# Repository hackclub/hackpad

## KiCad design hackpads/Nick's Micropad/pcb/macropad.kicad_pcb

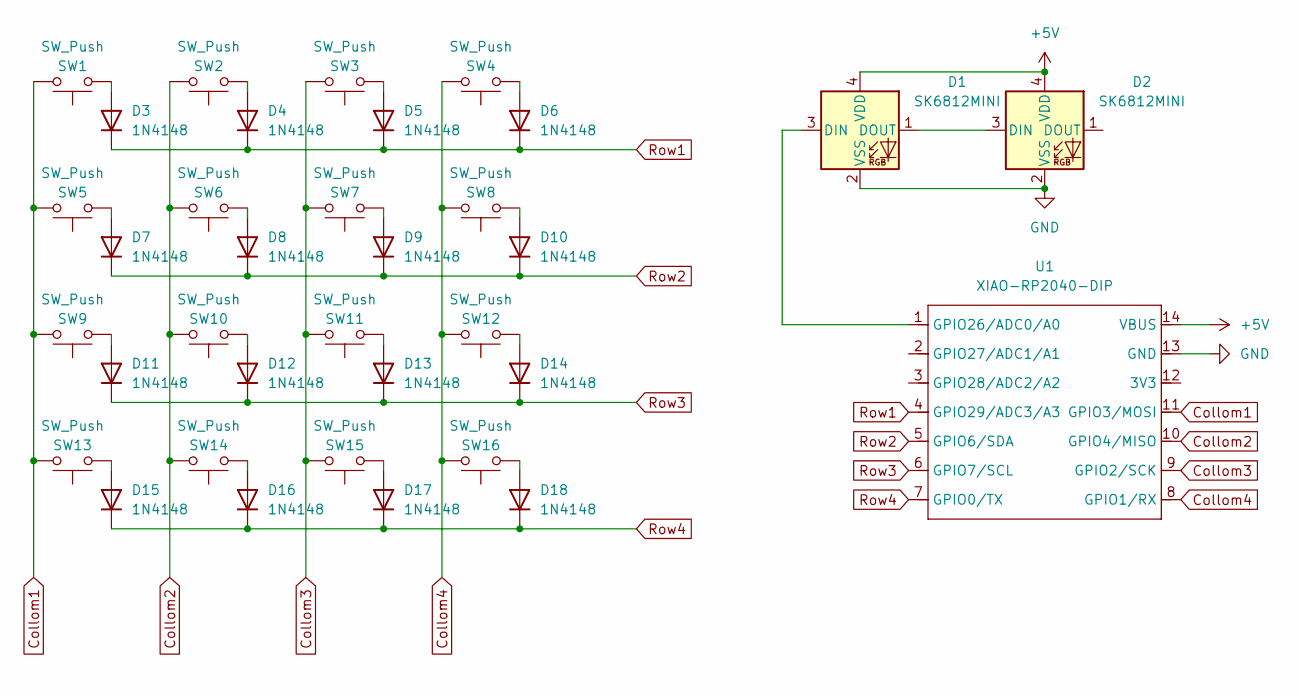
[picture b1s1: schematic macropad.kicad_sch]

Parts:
D1, D2: SK6812MINI; LED_SK6812MINI_PLCC4_3.5x3.5mm_P1.75mm
D3, D4, D5, D6, D7, D8, D9, D10, D11, D12, D13, D14, D15, D16, D17, D18: 1N4148; D_DO-35_SOD27_P7.62mm_Horizontal
SW1, SW2, SW3, SW4, SW5, SW6, SW7, SW8, SW9, SW10, SW11, SW12, SW13, SW14, SW15, SW16: SW_Push; SW_Cherry_MX_1.00u_PCB
U1: XIAO-RP2040-DIP

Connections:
+5V: D1.4 (VDD), D2.4 (VDD), U1.14 (VBUS)
Collom1: SW1.2, SW5.2, SW9.2, SW13.2, U1.11 (GPIO3/MOSI)
Collom2: SW2.2, SW6.2, SW10.2, SW14.2, U1.10 (GPIO4/MISO)
Collom3: SW3.2, SW7.2, SW11.2, SW15.2, U1.9 (GPIO2/SCK)
Collom4: SW4.2, SW8.2, SW12.2, SW16.2, U1.8 (GPIO1/RX)
GND: D1.2 (VSS), D2.2 (VSS), U1.13 (GND)
unnamed: D1.3 (DIN), U1.1 (GPIO26/ADC0/A0)
unnamed: D1.1 (DOUT), D2.3 (DIN)
unnamed: D3.2 (A), SW1.1
unnamed: D4.2 (A), SW2.1
unnamed: D5.2 (A), SW3.1
unnamed: D6.2 (A), SW4.1
unnamed: D7.2 (A), SW5.1
unnamed: D8.2 (A), SW6.1
unnamed: D9.2 (A), SW7.1
unnamed: D10.2 (A), SW8.1
unnamed: D11.2 (A), SW9.1
unnamed: D12.2 (A), SW10.1
unnamed: D13.2 (A), SW11.1
unnamed: D14.2 (A), SW12.1
unnamed: D15.2 (A), SW13.1
unnamed: D16.2 (A), SW14.1
unnamed: D17.2 (A), SW15.1
unnamed: D18.2 (A), SW16.1
Row1: D3.1 (K), D4.1 (K), D5.1 (K), D6.1 (K), U1.4 (GPIO29/ADC3/A3)
Row2: D7.1 (K), D8.1 (K), D9.1 (K), D10.1 (K), U1.5 (GPIO6/SDA)
Row3: D11.1 (K), D12.1 (K), D13.1 (K), D14.1 (K), U1.6 (GPIO7/SCL)
Row4: D15.1 (K), D16.1 (K), D17.1 (K), D18.1 (K), U1.7 (GPIO0/TX)

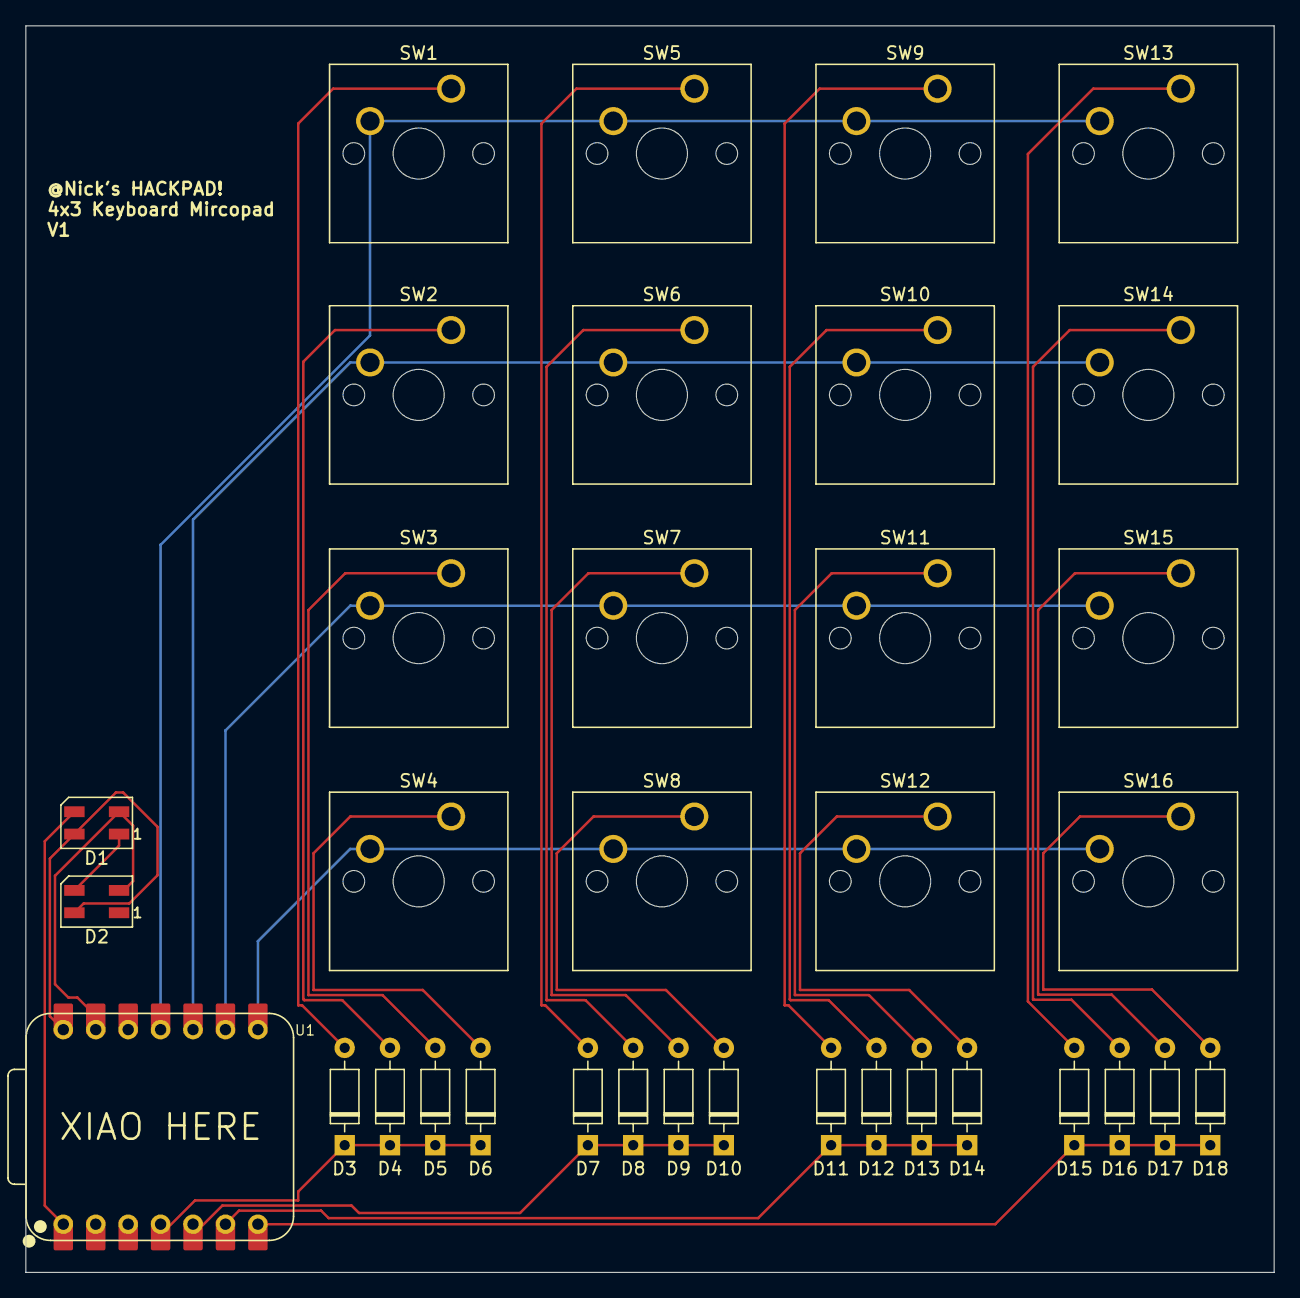
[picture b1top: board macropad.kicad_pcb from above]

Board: 2 copper layers, 97.8 x 97.6 mm, 35 parts (0 on the bottom side), 28 nets.

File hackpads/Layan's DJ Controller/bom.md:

# Hackpad - Bill of Materials

- 1x XIAO SEEED RP2040: XIAO-RP2040-DIP
- 1x MCP23017-SO: Package_SO:SOIC-28W_7.5x17.9mm_P1.27mm
- 2x LEDs: LED_SK6812MINI_PLCC4_3.5x3.5mm_P1.75mm
- 2x Bourns slide potentiometer: TRIM_PTA4543-2015DPA103
- 2x 4.7kΩ resistors: R_Axial_DIN0204_L3.6mm_D1.6mm_P7.62mm_Horizontal
- 8x Cherry MX switches: SW_Cherry_MX_1.00u_PCB
- 2x Alps rotary encoders: RotaryEncoder_Alps_EC11E_Vertical_H20mm

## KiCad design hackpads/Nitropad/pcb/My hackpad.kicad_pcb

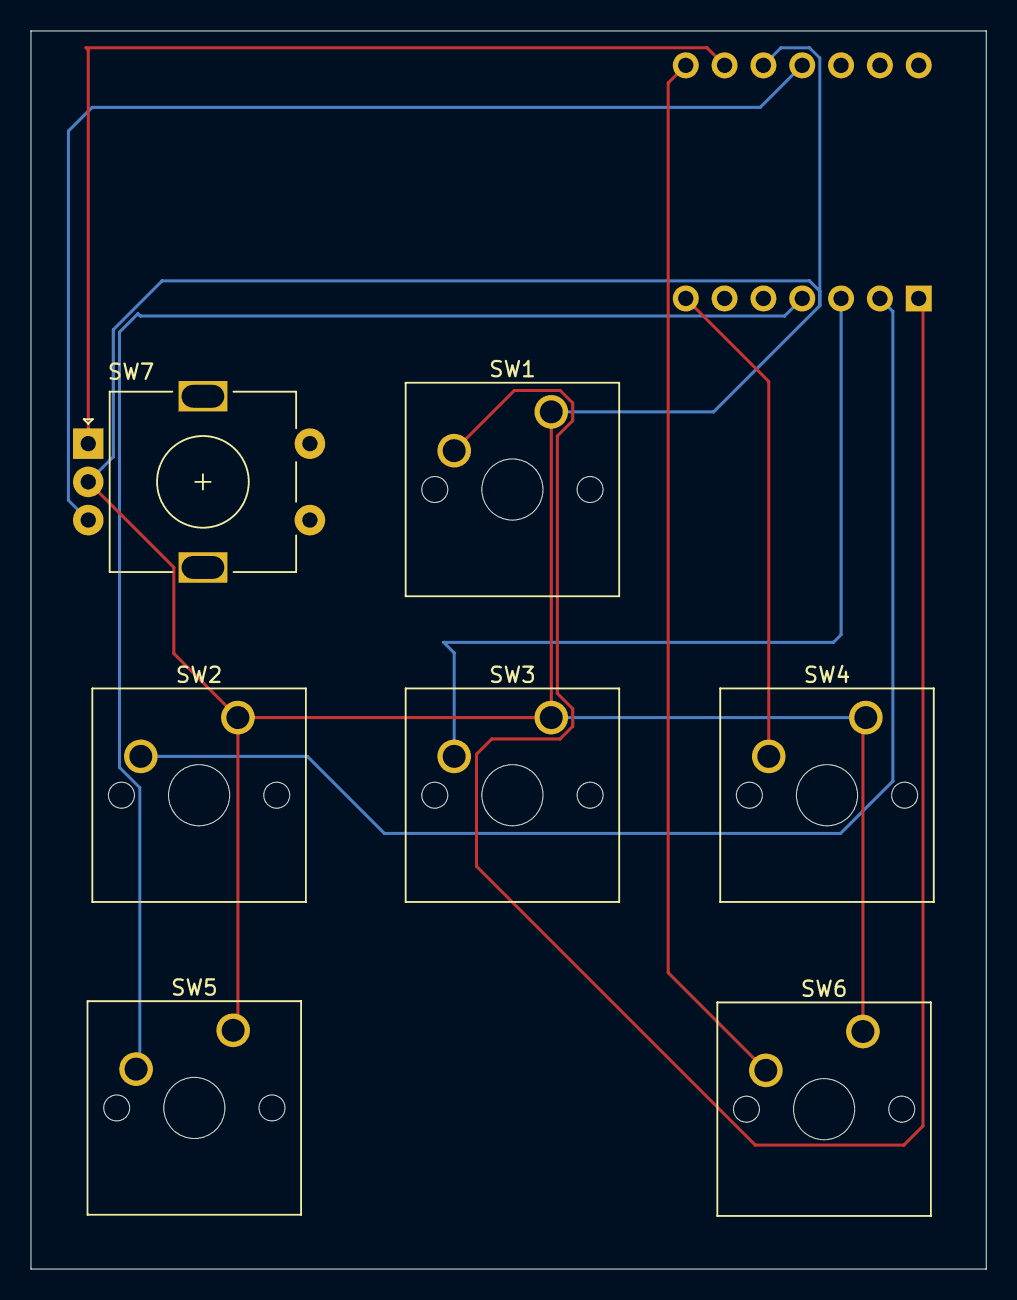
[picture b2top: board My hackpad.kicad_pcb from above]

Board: 2 copper layers, 62.5 x 81.0 mm, 8 parts (1 on the bottom side), 9 nets.

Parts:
SW1, SW2, SW3, SW4, SW5, SW6: SW_Push; SW_Cherry_MX_1.00u_PCB
SW7: RotaryEncoder; RotaryEncoder_Alps_EC11E-Switch_Vertical_H20mm
U1: Seeed Studio XIAO SAMD21; XIAO-Generic-Thruhole-14P-2.54-21X17.8MM

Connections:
1: SW1.2, U1.1 (PA02_A0_D0)
2: SW2.2, U1.2 (PA4_A1_D1)
3: SW3.2, U1.3 (PA10_A2_D2)
4: SW5.2, U1.4 (PA11_A3_D3)
5: SW4.2, U1.7 (PB08_A6_D6_TX)
6: SW6.2, U1.8 (PB09_A7_D7_RX)
A: SW7.A, U1.9 (PA7_A8_D8_SCK)
B: SW7.B, U1.11 (PA6_A10_D10_MOSI)
GND: SW1.1, SW2.1, SW3.1, SW4.1, SW5.1, SW6.1, SW7.C, U1.10 (PA5_A9_D9_MISO)

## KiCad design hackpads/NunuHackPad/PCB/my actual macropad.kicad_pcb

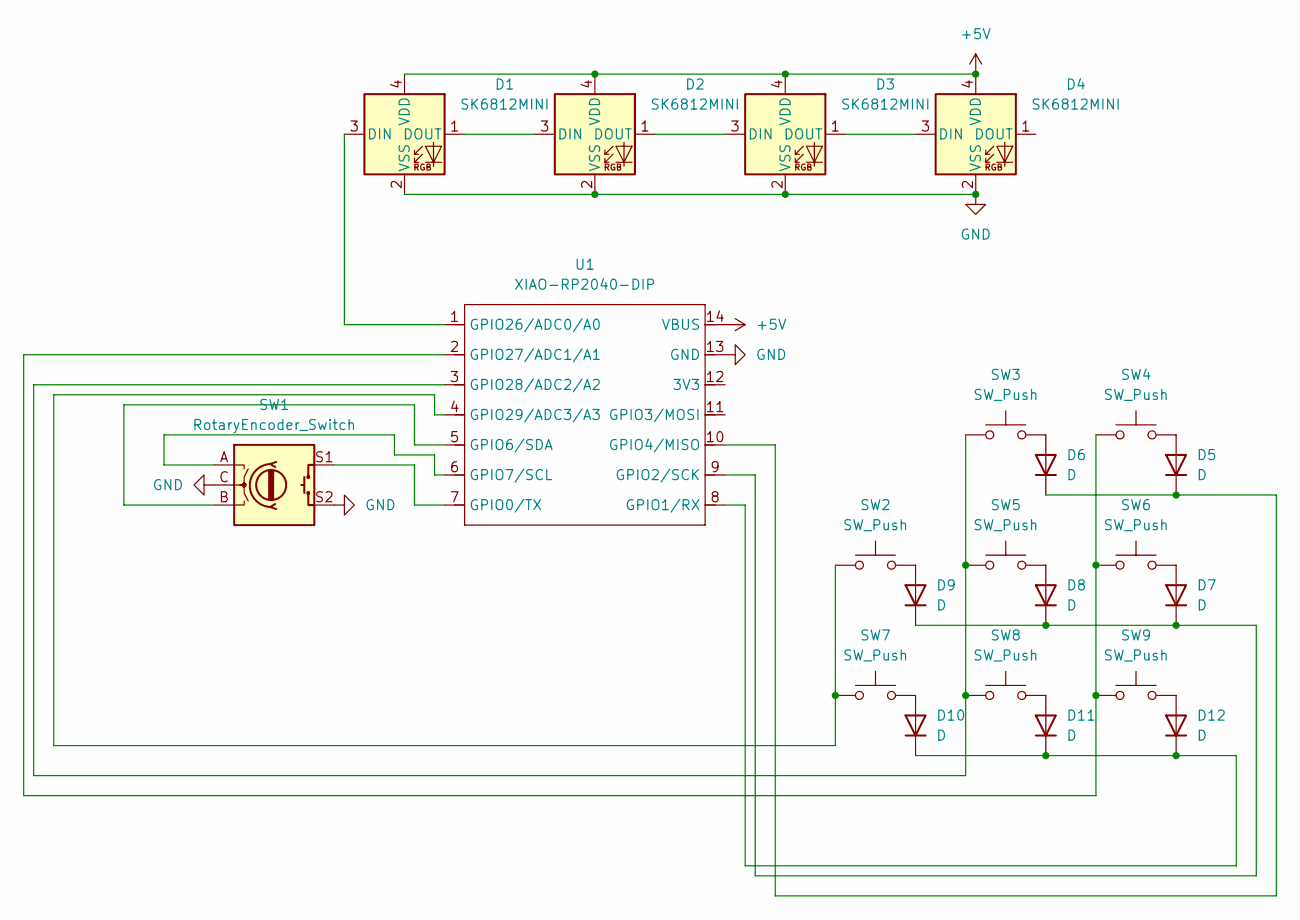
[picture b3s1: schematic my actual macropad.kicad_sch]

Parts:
D1, D2, D3, D4: SK6812MINI; LED_SK6812MINI_PLCC4_3.5x3.5mm_P1.75mm
D5, D6, D7, D8, D9, D10, D11, D12: D; D_DO-35_SOD27_P7.62mm_Horizontal
SW1: RotaryEncoder_Switch; RotaryEncoder_Alps_EC11E-Switch_Vertical_H20mm_CircularMoun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
SW2, SW3, SW4, SW5, SW6, SW7, SW8, SW9: SW_Push; SW_Cherry_MX_1.00u_PCB_3D
U1: XIAO-RP2040-DIP; XIAO-RP2040-DIP-3D

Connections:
+5V: D1.4 (VDD), D2.4 (VDD), D3.4 (VDD), D4.4 (VDD), U1.14 (VBUS)
GND: D1.2 (VSS), D2.2 (VSS), D3.2 (VSS), D4.2 (VSS), SW1.C, SW1.S2, U1.13 (GND)
unnamed: D1.3 (DIN), U1.1 (GPIO26/ADC0/A0)
unnamed: D1.1 (DOUT), D2.3 (DIN)
unnamed: D2.1 (DOUT), D3.3 (DIN)
unnamed: D3.1 (DOUT), D4.3 (DIN)
unnamed: D5.2 (A), SW4.2
unnamed: D5.1 (K), D6.1 (K), U1.10 (GPIO4/MISO)
unnamed: D6.2 (A), SW3.2
unnamed: D7.2 (A), SW6.2
unnamed: D7.1 (K), D8.1 (K), D9.1 (K), U1.9 (GPIO2/SCK)
unnamed: D8.2 (A), SW5.2
unnamed: D9.2 (A), SW2.2
unnamed: D10.2 (A), SW7.2
unnamed: D10.1 (K), D11.1 (K), D12.1 (K), U1.8 (GPIO1/RX)
unnamed: D11.2 (A), SW8.2
unnamed: D12.2 (A), SW9.2
unnamed: SW1.S1, U1.7 (GPIO0/TX)
unnamed: SW1.B, U1.5 (GPIO6/SDA)
unnamed: SW1.A, U1.6 (GPIO7/SCL)
unnamed: SW4.1, SW6.1, SW9.1, U1.2 (GPIO27/ADC1/A1)
unnamed: SW3.1, SW5.1, SW8.1, U1.3 (GPIO28/ADC2/A2)
unnamed: SW2.1, SW7.1, U1.4 (GPIO29/ADC3/A3)

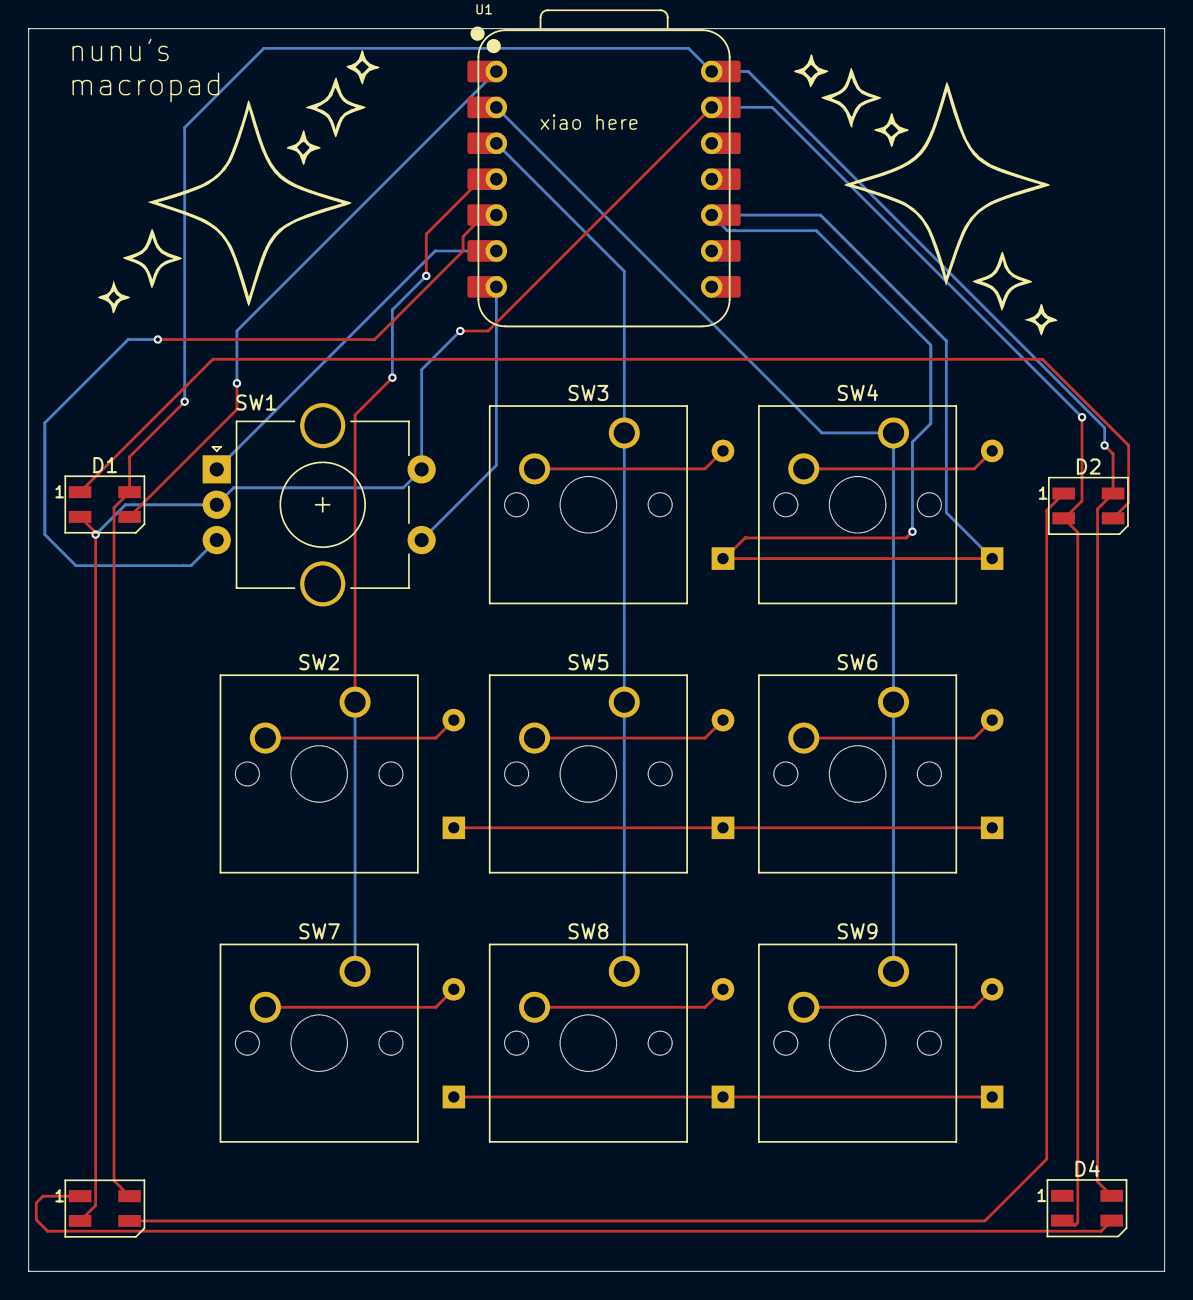
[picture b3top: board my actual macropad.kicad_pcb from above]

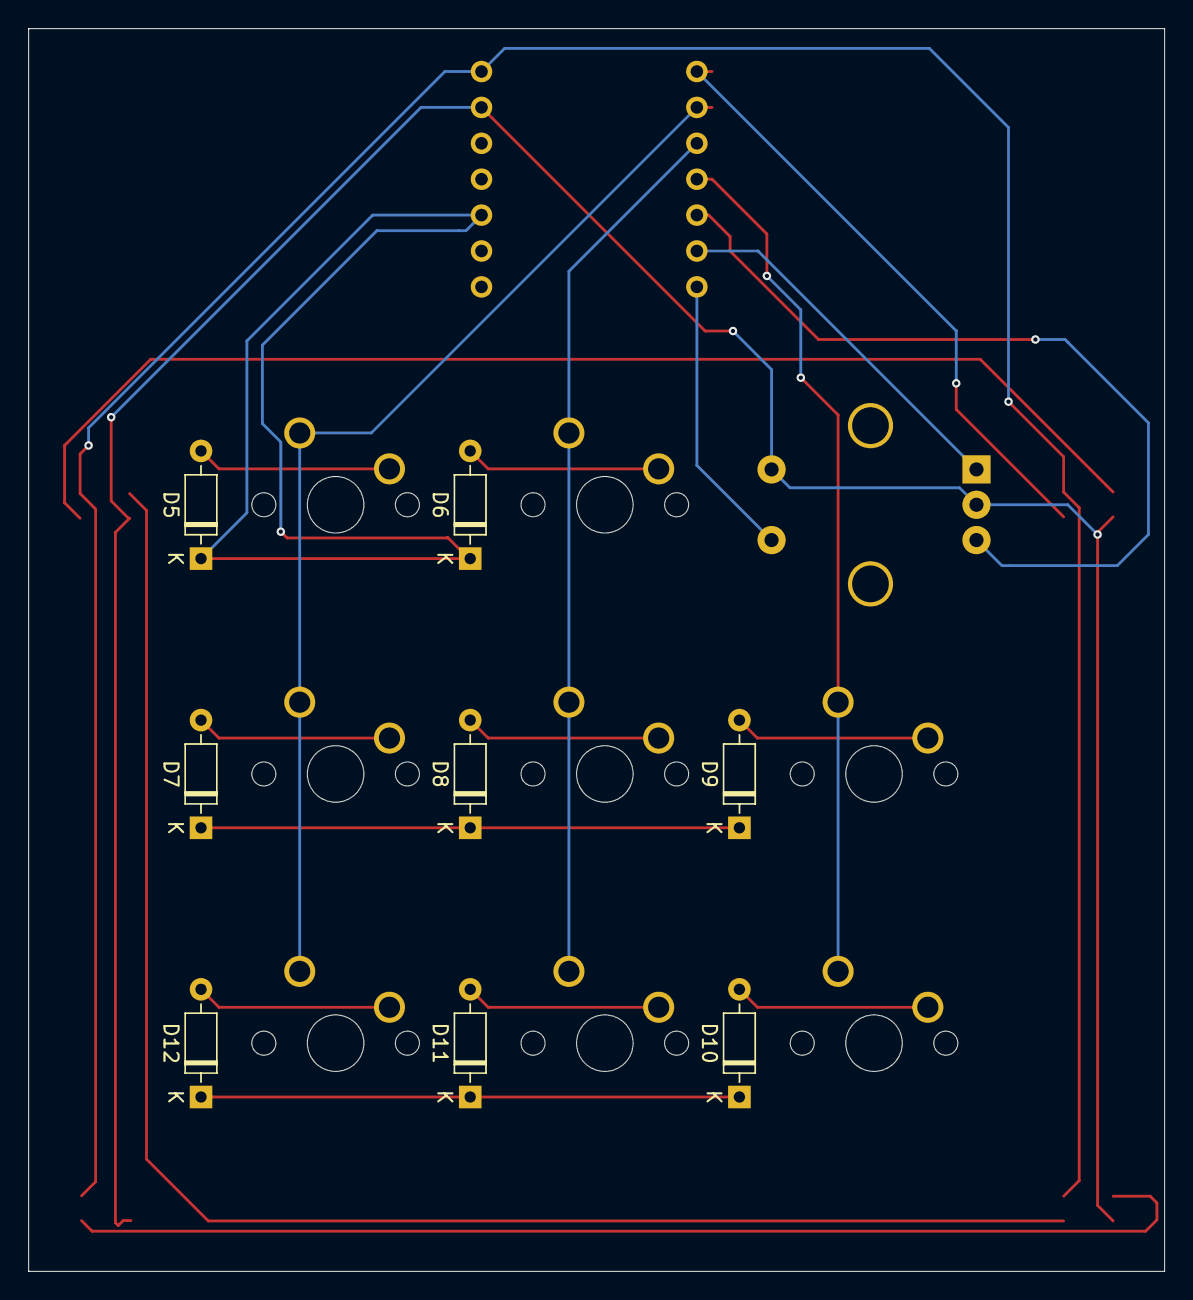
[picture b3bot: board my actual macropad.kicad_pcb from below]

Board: 2 copper layers, 80.4 x 87.9 mm, 22 parts (8 on the bottom side), 23 nets.

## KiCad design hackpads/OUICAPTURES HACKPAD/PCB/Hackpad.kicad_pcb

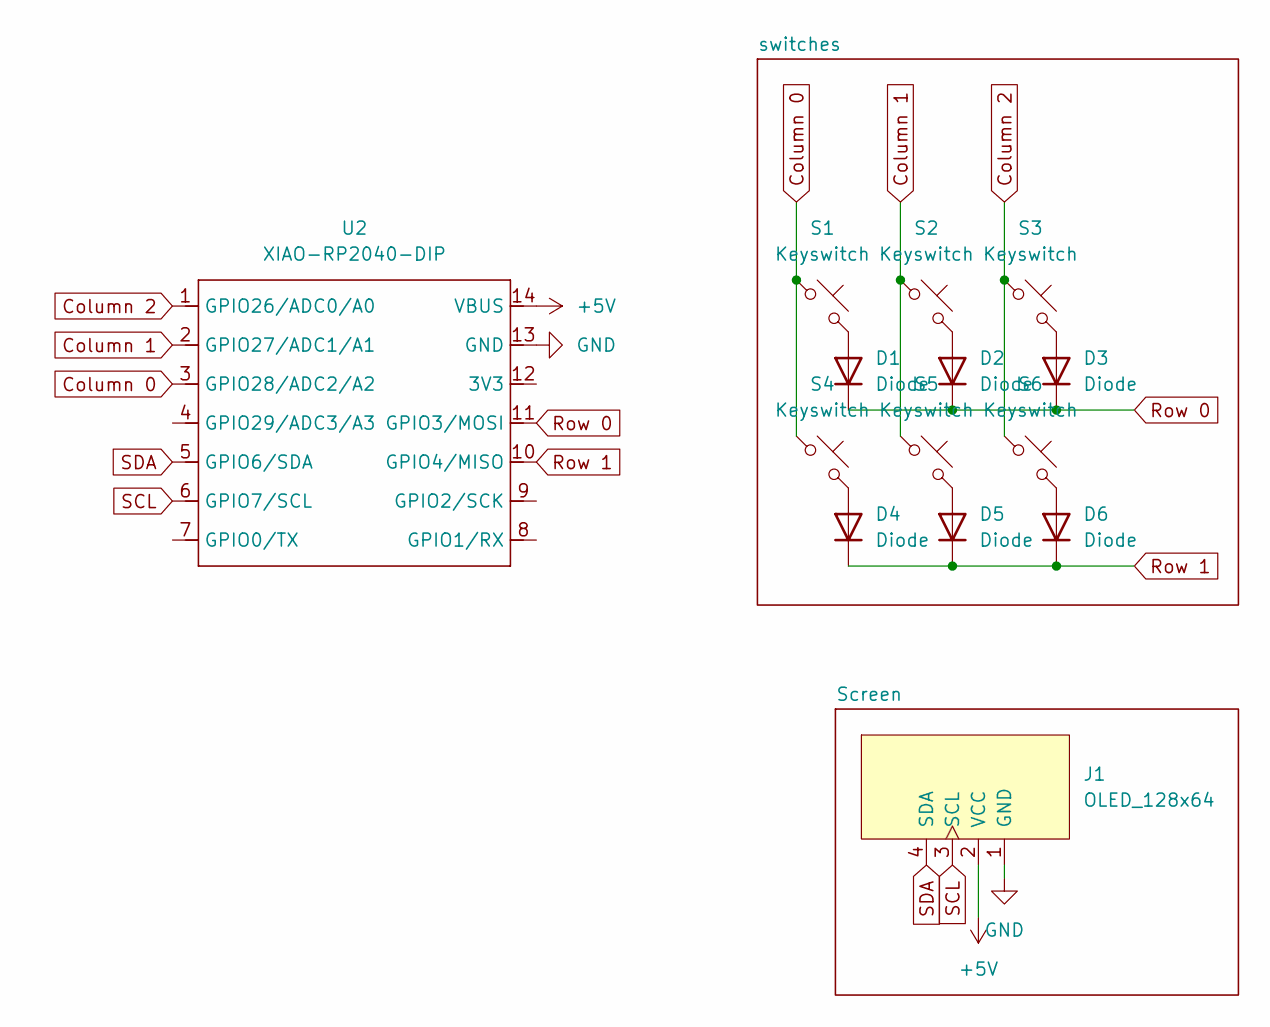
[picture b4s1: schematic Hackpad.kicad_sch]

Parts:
D1, D2, D3, D4, D5, D6: Diode; Diode_DO-35
J1: OLED_128x64
S1, S2, S3, S4, S5, S6: Keyswitch; MX_PCB_1.00u
U2: XIAO-RP2040-DIP; Seeed_XIAO_RP2040

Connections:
+5V: J1.2 (VCC), U2.14 (VBUS)
Column 0: S1.1, S4.1, U2.3 (GPIO28/ADC2/A2)
Column 1: S2.1, S5.1, U2.2 (GPIO27/ADC1/A1)
Column 2: S3.1, S6.1, U2.1 (GPIO26/ADC0/A0)
GND: J1.1 (GND), U2.13 (GND)
unnamed: D1.2 (A), S1.2
unnamed: D2.2 (A), S2.2
unnamed: D3.2 (A), S3.2
unnamed: D4.2 (A), S4.2
unnamed: D5.2 (A), S5.2
unnamed: D6.2 (A), S6.2
Row 0: D1.1 (K), D2.1 (K), D3.1 (K), U2.11 (GPIO3/MOSI)
Row 1: D4.1 (K), D5.1 (K), D6.1 (K), U2.10 (GPIO4/MISO)
SCL: J1.3 (SCL), U2.6 (GPIO7/SCL)
SDA: J1.4 (SDA), U2.5 (GPIO6/SDA)

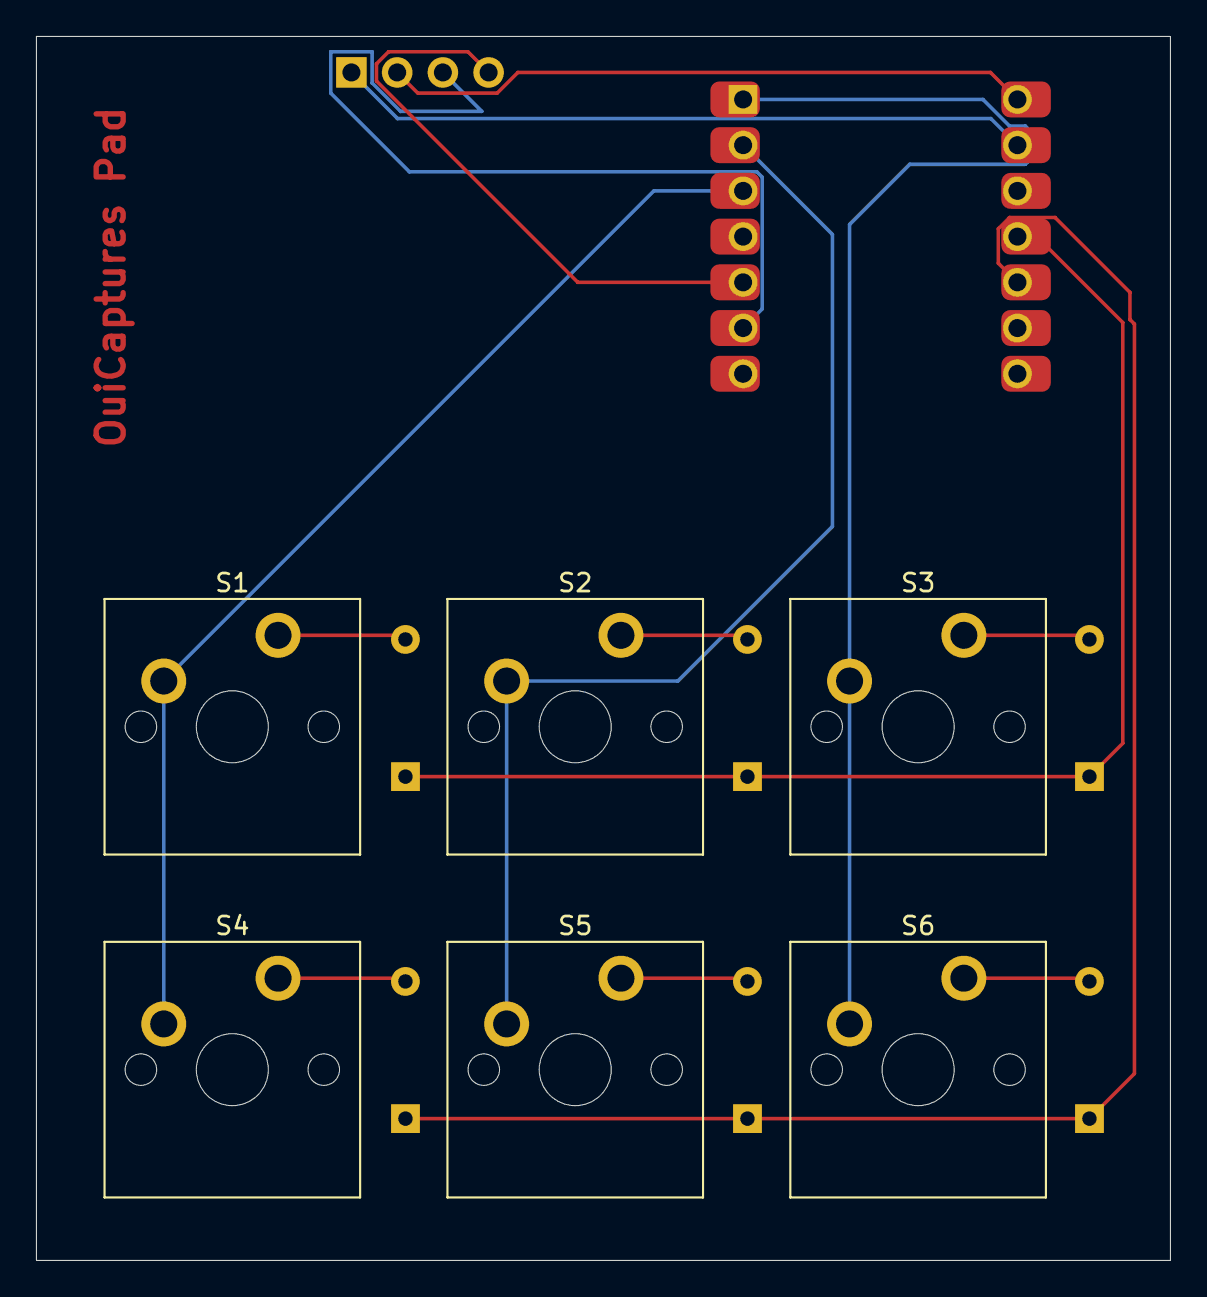
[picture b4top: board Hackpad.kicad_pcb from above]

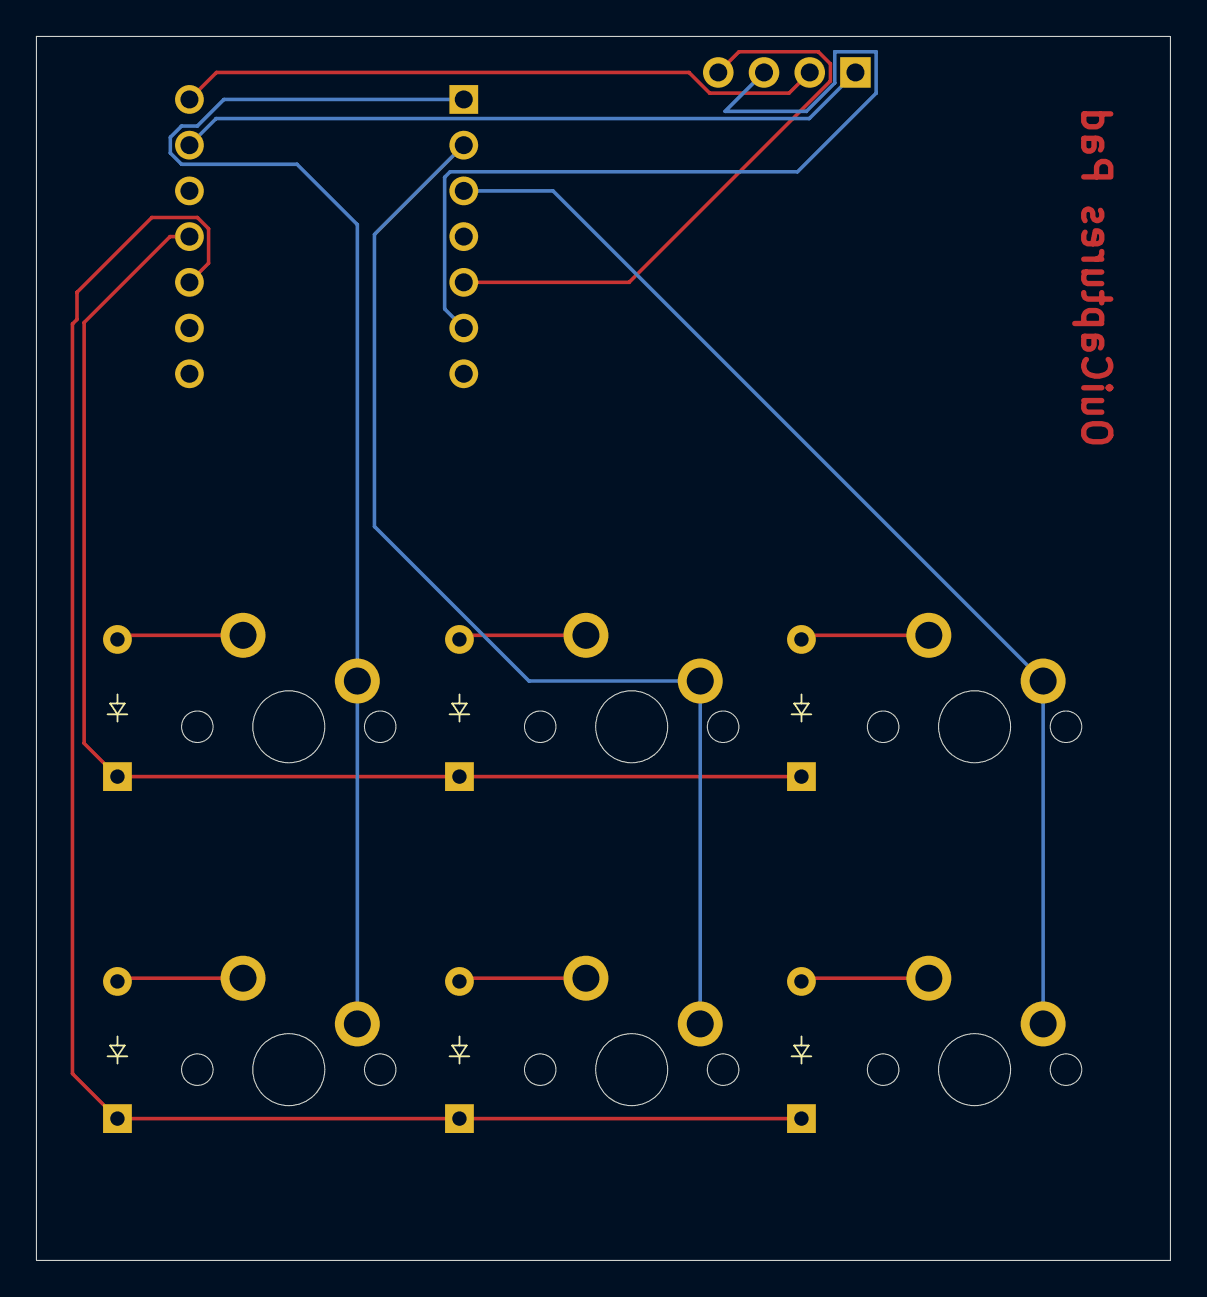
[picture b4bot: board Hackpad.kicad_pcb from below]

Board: 2 copper layers, 63.0 x 68.0 mm, 14 parts (6 on the bottom side), 15 nets.

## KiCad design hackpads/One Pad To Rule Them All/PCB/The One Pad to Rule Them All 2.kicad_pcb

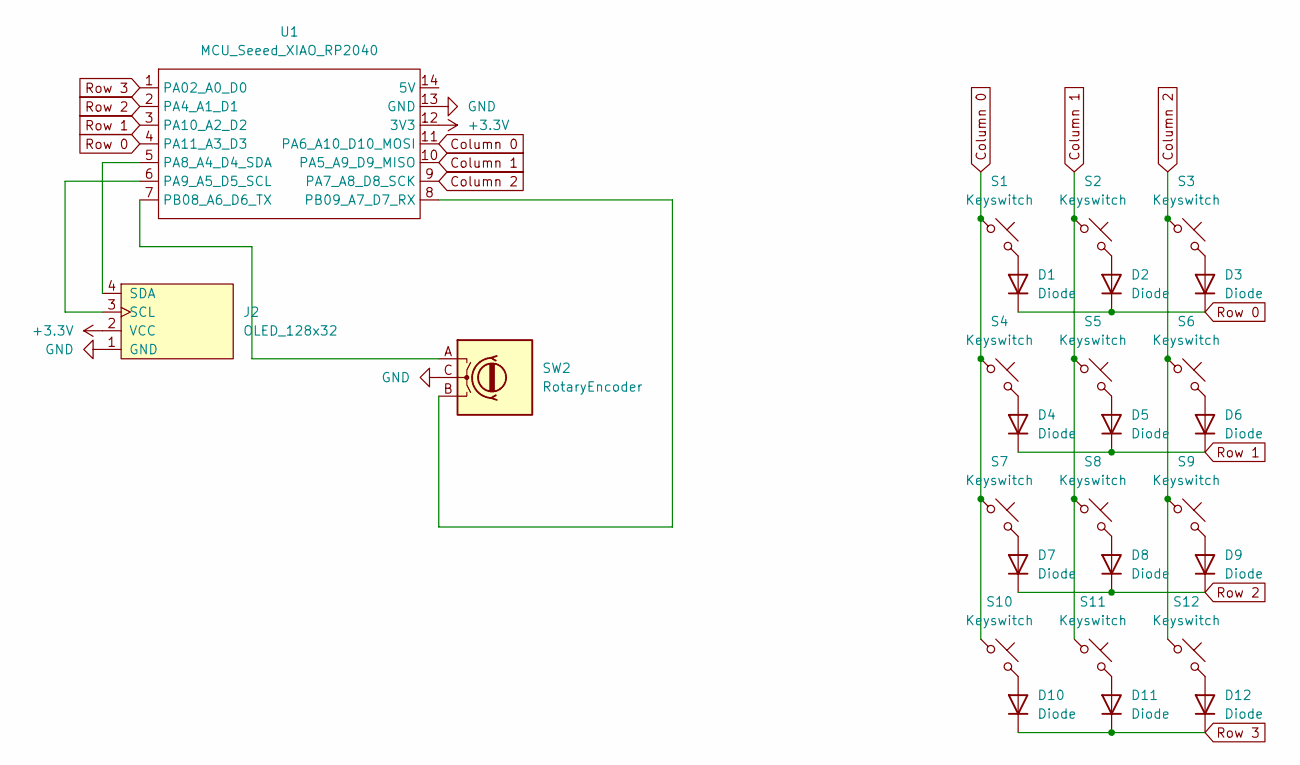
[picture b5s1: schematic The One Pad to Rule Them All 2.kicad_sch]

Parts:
D1, D2, D3, D4, D5, D6, D7, D8, D9, D10, D11, D12: Diode; Diode_DO-35
J2: OLED_128x32
S1, S2, S3, S4, S5, S6, S7, S8, S9, S10, S11, S12: Keyswitch; MX_PCB_1.00u
SW2: RotaryEncoder; RotaryEncoder_Alps_EC11E_Vertical_H20mm
U1: MCU_Seeed_XIAO_RP2040; Seeed_XIAO_RP2040

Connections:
+3.3V: J2.2 (VCC), U1.12 (3V3)
Column 0: S1.1, S4.1, S7.1, S10.1, U1.11 (PA6_A10_D10_MOSI)
Column 1: S2.1, S5.1, S8.1, S11.1, U1.10 (PA5_A9_D9_MISO)
Column 2: S3.1, S6.1, S9.1, S12.1, U1.9 (PA7_A8_D8_SCK)
GND: J2.1 (GND), SW2.C, U1.13 (GND)
unnamed: D1.2 (A), S1.2
unnamed: D2.2 (A), S2.2
unnamed: D3.2 (A), S3.2
unnamed: D4.2 (A), S4.2
unnamed: D5.2 (A), S5.2
unnamed: D6.2 (A), S6.2
unnamed: D7.2 (A), S7.2
unnamed: D8.2 (A), S8.2
unnamed: D9.2 (A), S9.2
unnamed: D10.2 (A), S10.2
unnamed: D11.2 (A), S11.2
unnamed: D12.2 (A), S12.2
unnamed: J2.3 (SCL), U1.6 (PA9_A5_D5_SCL)
unnamed: J2.4 (SDA), U1.5 (PA8_A4_D4_SDA)
unnamed: SW2.A, U1.7 (PB08_A6_D6_TX)
unnamed: SW2.B, U1.8 (PB09_A7_D7_RX)
Row 0: D1.1 (K), D2.1 (K), D3.1 (K), U1.4 (PA11_A3_D3)
Row 1: D4.1 (K), D5.1 (K), D6.1 (K), U1.3 (PA10_A2_D2)
Row 2: D7.1 (K), D8.1 (K), D9.1 (K), U1.2 (PA4_A1_D1)
Row 3: D10.1 (K), D11.1 (K), D12.1 (K), U1.1 (PA02_A0_D0)

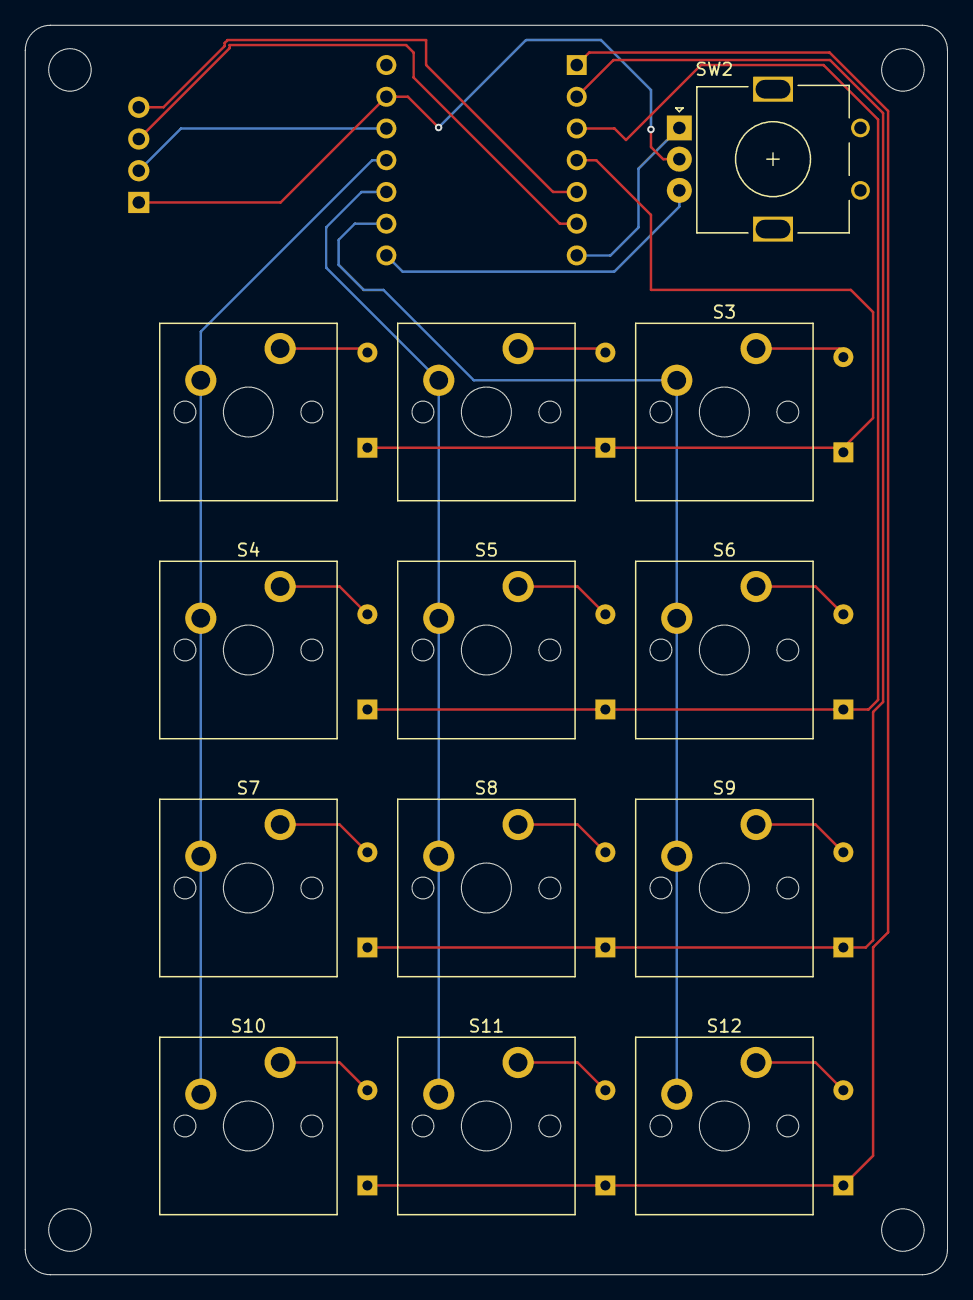
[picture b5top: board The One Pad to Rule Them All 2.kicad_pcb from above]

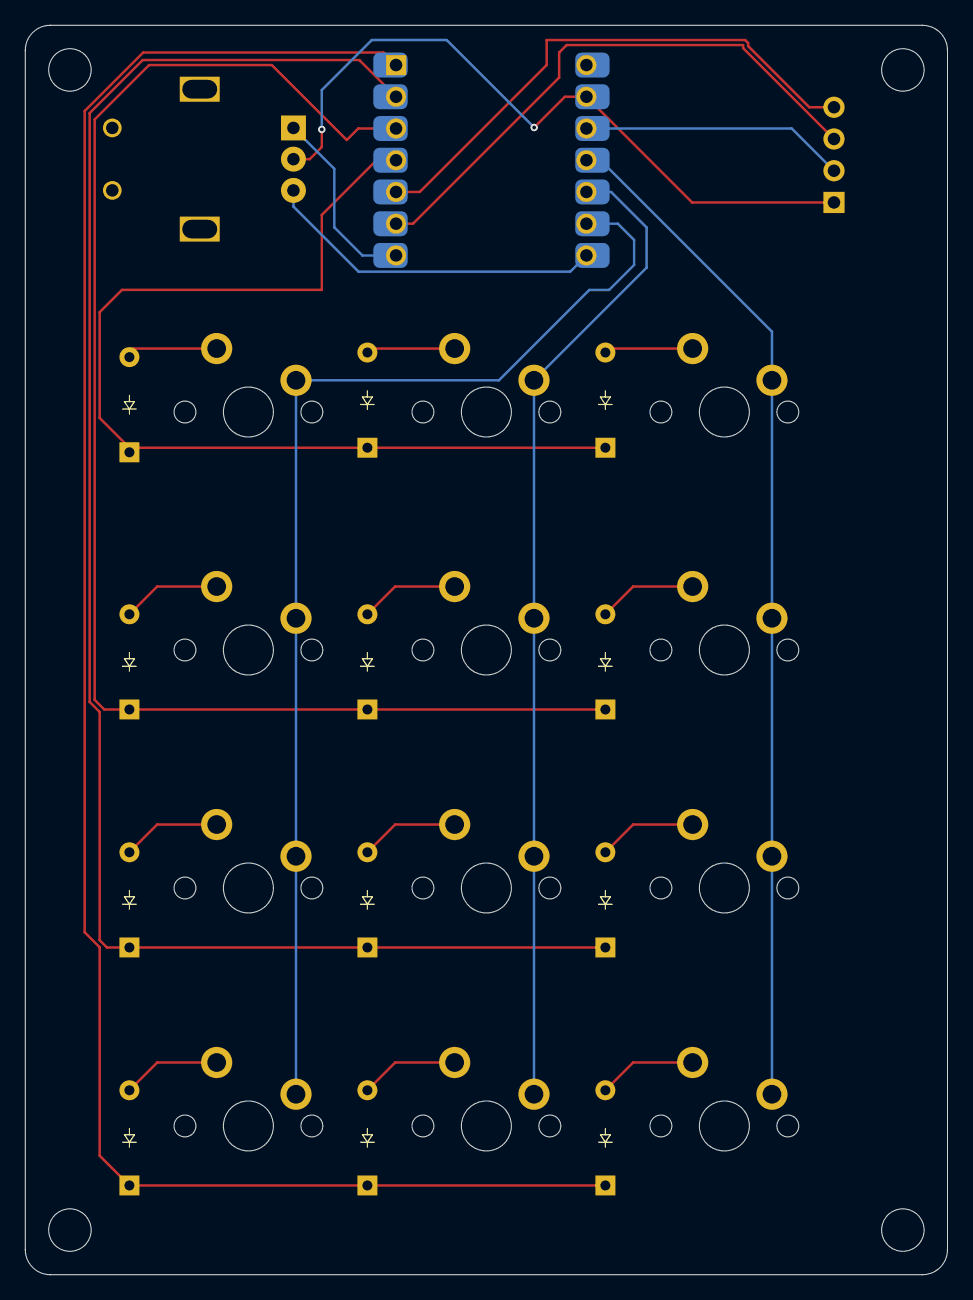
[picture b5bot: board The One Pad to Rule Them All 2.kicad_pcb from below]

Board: 2 copper layers, 73.8 x 100.0 mm, 27 parts (13 on the bottom side), 25 nets.

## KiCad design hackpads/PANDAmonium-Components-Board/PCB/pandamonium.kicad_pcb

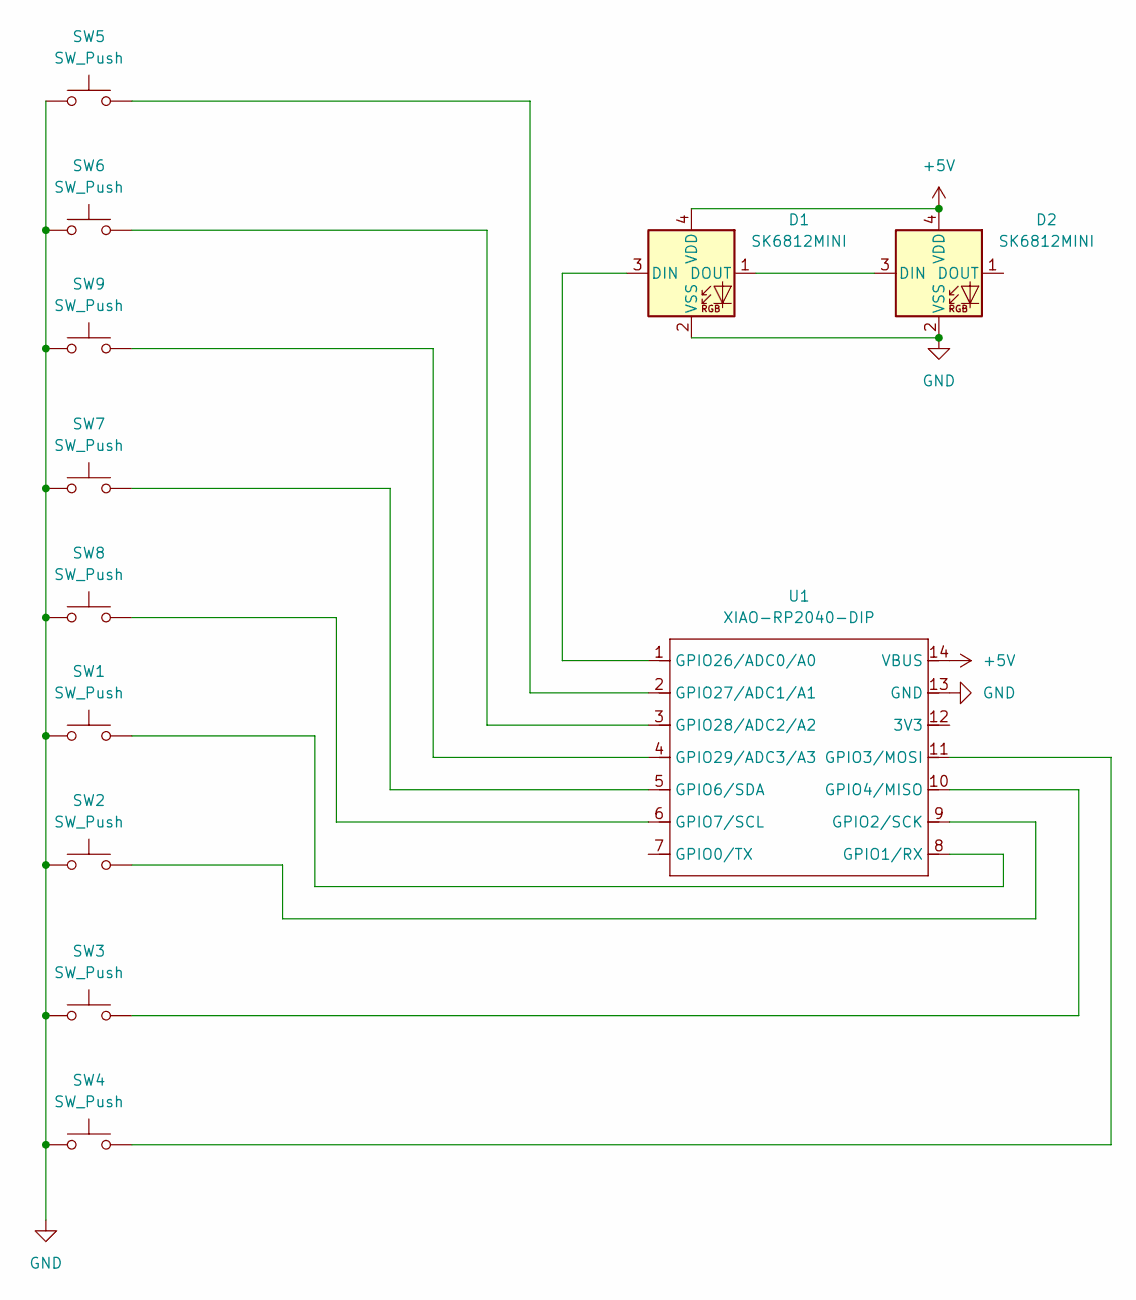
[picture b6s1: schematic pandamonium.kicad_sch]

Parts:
D1, D2: SK6812MINI; LED_SK6812MINI_PLCC4_3.5x3.5mm_P1.75mm
SW1, SW2, SW3, SW4, SW5, SW6, SW7, SW8, SW9: SW_Push; SW_Cherry_MX_1.00u_PCB
U1: XIAO-RP2040-DIP

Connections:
+5V: D1.4 (VDD), D2.4 (VDD), U1.14 (VBUS)
GND: D1.2 (VSS), D2.2 (VSS), SW1.1, SW2.1, SW3.1, SW4.1, SW5.1, SW6.1, SW7.1, SW8.1, SW9.1, U1.13 (GND)
unnamed: D1.3 (DIN), U1.1 (GPIO26/ADC0/A0)
unnamed: D1.1 (DOUT), D2.3 (DIN)
unnamed: SW1.2, U1.8 (GPIO1/RX)
unnamed: SW2.2, U1.9 (GPIO2/SCK)
unnamed: SW4.2, U1.11 (GPIO3/MOSI)
unnamed: SW3.2, U1.10 (GPIO4/MISO)
unnamed: SW7.2, U1.5 (GPIO6/SDA)
unnamed: SW8.2, U1.6 (GPIO7/SCL)
unnamed: SW5.2, U1.2 (GPIO27/ADC1/A1)
unnamed: SW6.2, U1.3 (GPIO28/ADC2/A2)
unnamed: SW9.2, U1.4 (GPIO29/ADC3/A3)
